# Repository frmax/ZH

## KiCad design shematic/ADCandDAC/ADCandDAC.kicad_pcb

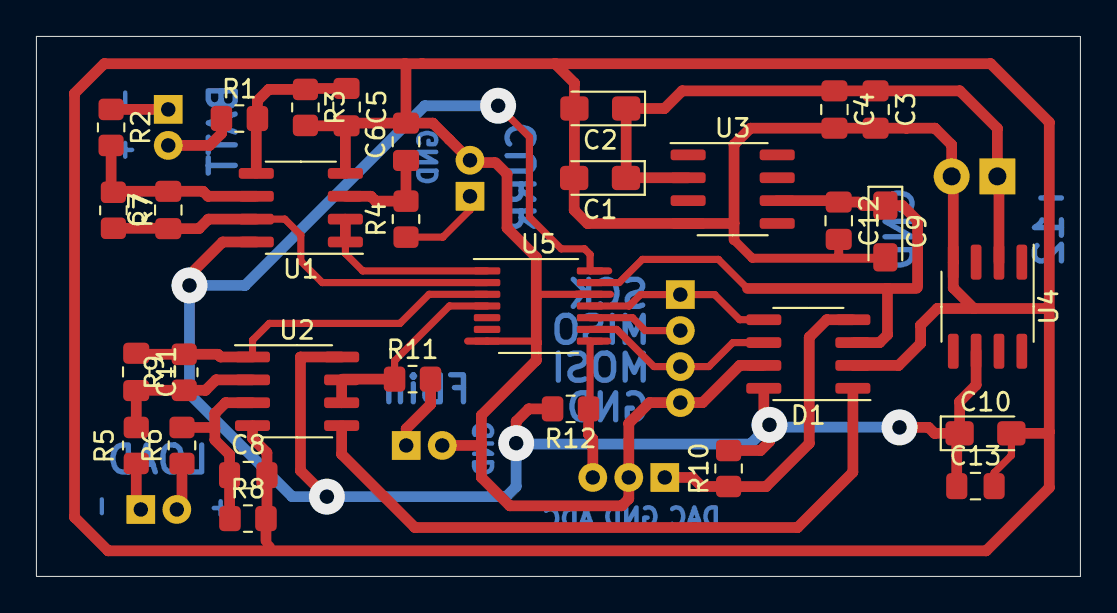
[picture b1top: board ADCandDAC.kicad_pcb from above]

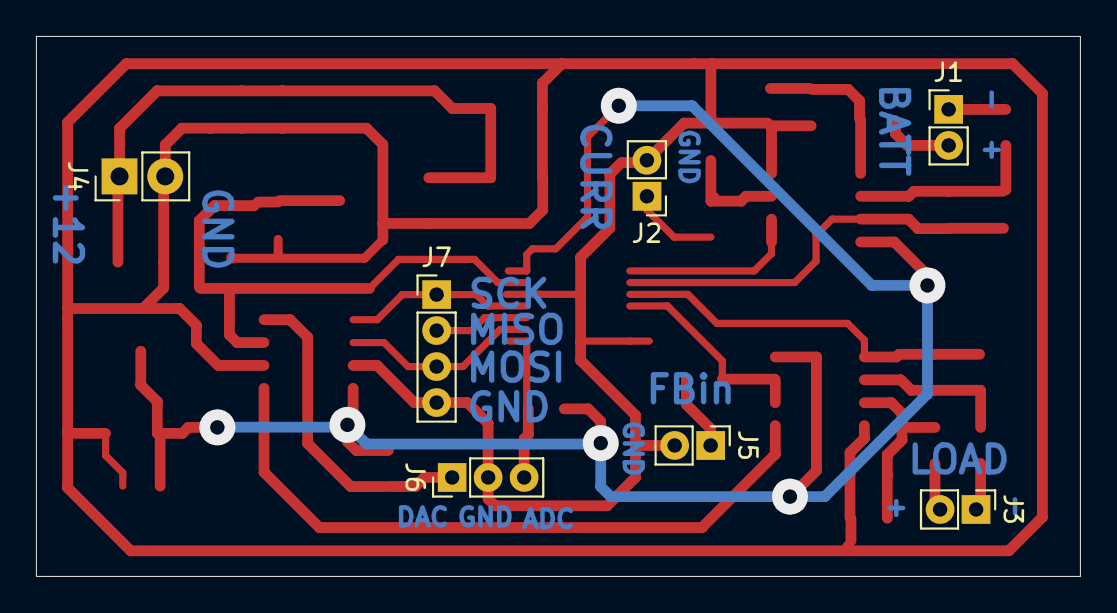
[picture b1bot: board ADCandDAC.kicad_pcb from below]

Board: 2 copper layers, 58.0 x 30.0 mm, 38 parts (7 on the bottom side), 25 nets.

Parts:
C1, C2: 10u; CP_EIA-3216-18_Kemet-A_Pad1.58x1.35mm_HandSolder
C3, C4, C5, C6, C7, C8, C11, C12, C13: 100n; C_0805_2012Metric_Pad1.18x1.45mm_HandSolder
C9, C10: 1u; CP_EIA-3216-18_Kemet-A_Pad1.58x1.35mm_HandSolder
D1: dac8830; SOIC-8_3.9x4.9mm_P1.27mm
J1: Battery; PinHeader_1x02_P2.00mm_Vertical
J2: Current; PinHeader_1x02_P2.00mm_Vertical
J3: Loading; PinHeader_1x02_P2.00mm_Vertical
J4: VCC_12V; PinHeader_1x02_P2.54mm_Vertical
J5: FBin; PinHeader_1x02_P2.00mm_Vertical
J6: CS; PinHeader_1x03_P2.00mm_Vertical
J7: SPI; PinHeader_1x04_P2.00mm_Vertical
R1, R2, R5, R6: 10k; R_0805_2012Metric_Pad1.20x1.40mm_HandSolder
R3, R4, R7, R8, R9: 1k; R_0805_2012Metric_Pad1.20x1.40mm_HandSolder
R10, R12: 100k; R_0805_2012Metric_Pad1.20x1.40mm_HandSolder
R11: 5,9k; R_0805_2012Metric_Pad1.20x1.40mm_HandSolder
U1, U2: AD8552ARZ; SOIC-8_3.9x4.9mm_P1.27mm
U3: REF198; SOIC-8_3.9x4.9mm_P1.27mm
U4: REF195; SOIC-8_3.9x4.9mm_P1.27mm
U5: MCP3204; TSSOP-14_4.4x5mm_P0.65mm

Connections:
/DACgen: D1.1, U2.5
/REF+4: C9.1, C12.1, D1.3, U3.6, U5.13
/REF+5: C10.1, C13.1, D1.8, R10.2, R12.2, U1.8, U2.8, U4.6, U5.14
ADC: J6.3, R12.1, U5.8
DAC: D1.4, J6.1, R10.1
GND: C1.2, C2.2, C3.2, C4.2, C5.2, C6.2, C8.2, C9.2, C10.2, C12.2, C13.2, D1.2, D1.7, J2.2, J4.2, J5.2, J6.2, J7.4, R3.2, R8.2, U1.4, U2.4, U3.4, U4.4, U5.7, U5.12
MISO: J7.2, U5.10
MOSI: D1.6, J7.3, U5.9
unnamed: C5.1, R1.2, R3.1, U1.5
unnamed: C6.1, R4.2, U1.3
unnamed: C7.1, R7.2, U1.7, U5.2
unnamed: C7.2, R2.2, R7.1, U1.6
unnamed: C8.1, R6.2, R8.1, U2.3
unnamed: C11.1, R9.2, U2.1, U5.3
unnamed: C11.2, R5.2, R9.1, U2.2
unnamed: J1.1, R2.1
unnamed: J1.2, R1.1
unnamed: J2.1, R4.1
unnamed: J3.1, R5.1
unnamed: J3.2, R6.1
unnamed: J5.1, R11.2
unnamed: R11.1, U2.6, U2.7, U5.4
unnamed: U1.1, U1.2, U5.1
SCK: D1.5, J7.1, U5.11
VCC_12V: C1.1, C2.1, C3.1, C4.1, J4.1, U3.2, U4.2

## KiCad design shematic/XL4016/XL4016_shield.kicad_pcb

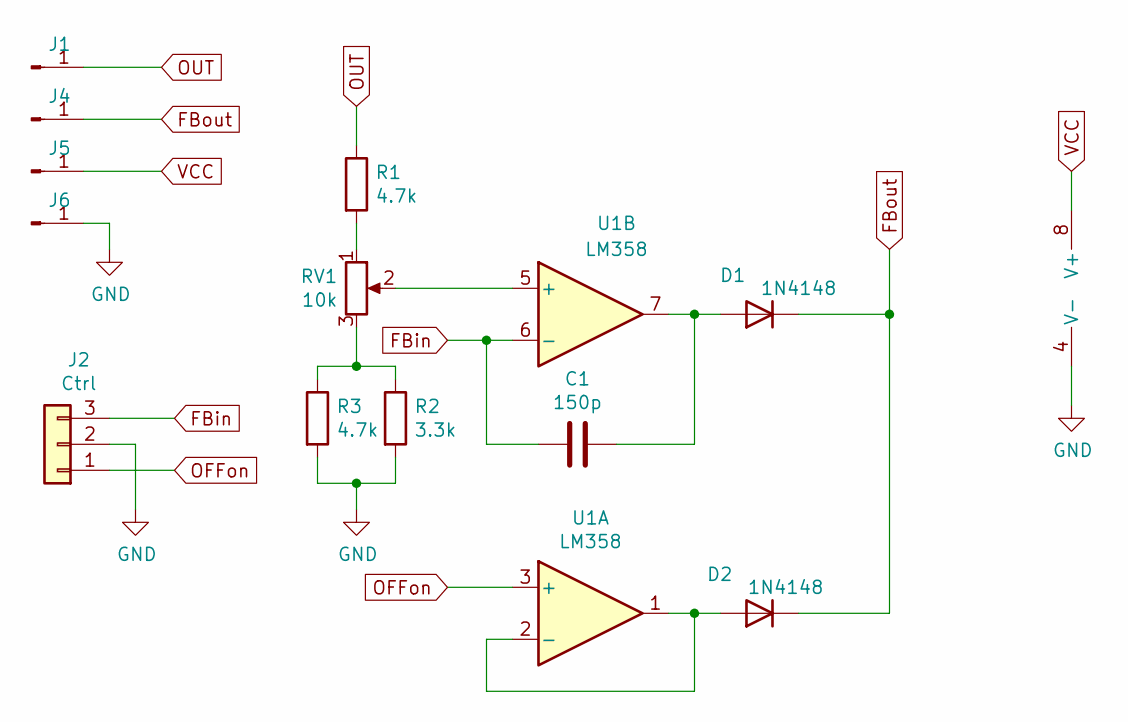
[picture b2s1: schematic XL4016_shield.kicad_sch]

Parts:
C1: 150p; C_0603_1608Metric_Pad1.08x0.95mm_HandSolder
D1, D2: 1N4148; D_SOD-123
J1: OUT+; Pin_D0.7mm_L6.5mm_W1.8mm_FlatFork
J2: Ctrl; PinHeader_1x03_P2.54mm_Vertical
J4: FBout; Pin_D0.7mm_L6.5mm_W1.8mm_FlatFork
J5: VCC; Pin_D0.7mm_L6.5mm_W1.8mm_FlatFork
J6: GND; Pin_D0.7mm_L6.5mm_W1.8mm_FlatFork
R1, R3: 4.7k; R_0603_1608Metric_Pad0.98x0.95mm_HandSolder
R2: 3.3k; R_0603_1608Metric_Pad0.98x0.95mm_HandSolder
RV1: 10k; Potentiometer_Bourns_3386C_Horizontal
U1: LM358; SO-8_3.9x4.9mm_P1.27mm

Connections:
FBin: C1.2, J2.3, U1.6 (-)
FBout: D1.1 (K), D2.1 (K), J4.1
GND: J2.2, J6.1, R2.2, R3.2, U1.4 (V-)
unnamed: C1.1, D1.2 (A), U1.7
unnamed: D2.2 (A), U1.1, U1.2 (-)
unnamed: R1.2, RV1.1
unnamed: R2.1, R3.1, RV1.3
unnamed: RV1.2, U1.5 (+)
OFFon: J2.1, U1.3 (+)
OUT: J1.1, R1.1
VCC: J5.1, U1.8 (V+)

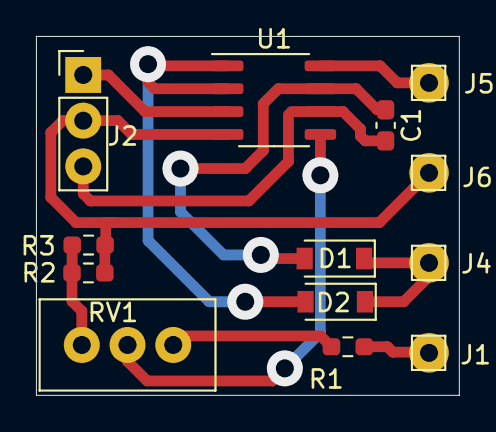
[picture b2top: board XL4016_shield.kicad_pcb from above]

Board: 2 copper layers, 23.5 x 19.9 mm, 13 parts (0 on the bottom side), 11 nets.

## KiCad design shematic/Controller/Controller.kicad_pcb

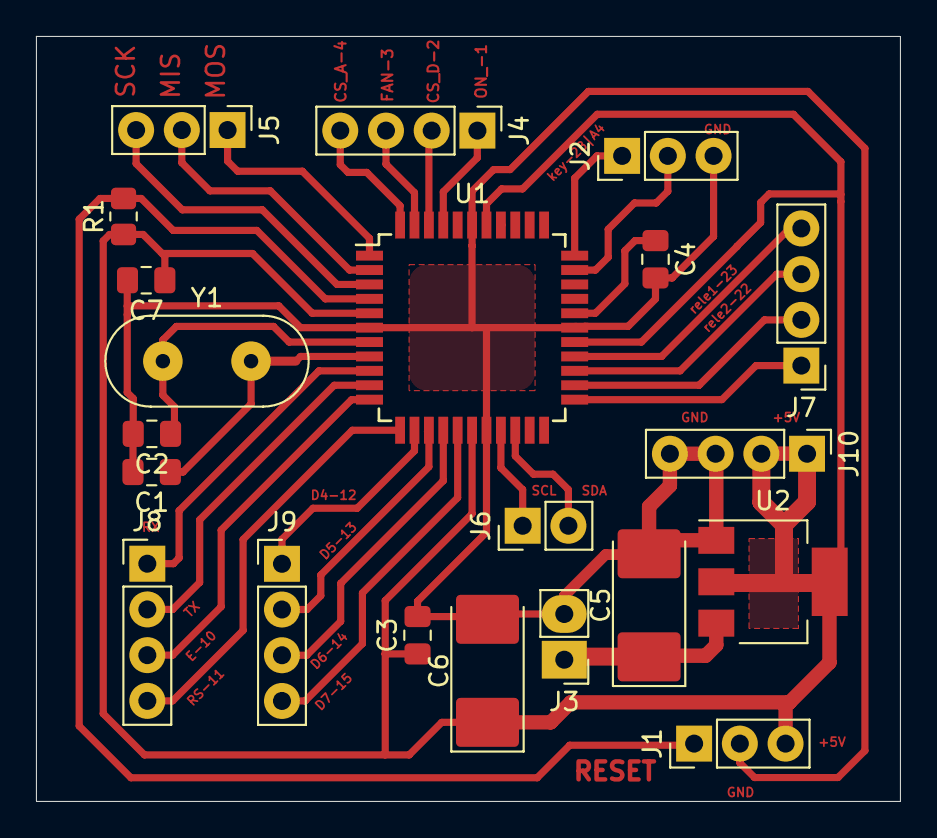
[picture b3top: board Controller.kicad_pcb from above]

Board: 2 copper layers, 48.0 x 42.5 mm, 21 parts (0 on the bottom side), 30 nets.

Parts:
C1, C2: 20p; C_0805_2012Metric_Pad1.18x1.45mm_HandSolder
C3, C4, C7: 100n; C_0805_2012Metric_Pad1.18x1.45mm_HandSolder
C5, C6: 47u; CP_EIA-7132-20_AVX-U_Pad2.72x3.50mm_HandSolder
J1: RESET; PinHeader_1x03_P2.54mm_Vertical
J2: Analog; PinHeader_1x03_P2.54mm_Vertical
J3: +12; PinHeader_1x02_P2.54mm_Vertical
J4: CS_FAN_ONOFF; PinHeader_1x04_P2.54mm_Vertical
J5: SPI; PinHeader_1x03_P2.54mm_Vertical
J6: I2C; PinHeader_1x02_P2.54mm_Vertical
J7: RELE_T; PinHeader_1x04_P2.54mm_Vertical
J8: RxTx/Display_1; PinHeader_1x04_P2.54mm_Vertical
J9: Display_2; PinHeader_1x04_P2.54mm_Vertical
J10: +5_GND; PinHeader_1x04_P2.54mm_Vertical
R1: 10k; R_0805_2012Metric_Pad1.20x1.40mm_HandSolder
U1: ATmega16A-AU; TQFP-44_10x10mm_P0.8mm
U2: AMS1117-5.0; SOT-223-3_TabPin2
Y1: Crystal; Crystal_HC18-U_Vertical

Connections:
+5V: C3.1, C6.1, C7.1, J1.3, J10.1, J10.2, R1.1, U1.5, U1.17, U1.27, U1.38, U2.2
+12V: C5.1, J3.1, U2.3
/CS_A-4: J4.4, U1.44
/CS_D-2: J4.2, U1.42
/D4-12: J9.1, U1.13
/D5-13: J9.2, U1.14
/D6-14: J9.3, U1.15
/D7-15: J9.4, U1.16
/E-10: J8.3, U1.11
/FAN-3: J4.3, U1.43
/KEY_-28|A4: J2.1, U1.33
/MISO: J5.2, U1.2
/MOSI: J5.1, U1.1
/ON_-1: J4.1, U1.41
/RELE_1-23: J7.4, U1.26
/RELE_2-22: J7.3, U1.25
/RS-11: J8.4, U1.12
/RX: J8.1, U1.9
/SCK: J5.3, U1.3
/SCL: J6.1, U1.19
/SDA: J6.2, U1.20
/TX: J8.2, U1.10
GND: C1.2, C2.2, C3.2, C4.2, C5.2, C6.2, C7.2, J1.2, J2.3, J3.2, J10.3, J10.4, U1.6, U1.18, U1.28, U1.39, U2.1
unnamed: C1.1, U1.8, Y1.2
unnamed: C2.1, U1.7, Y1.1
unnamed: C4.1, U1.29
unnamed: J2.2, U1.32
unnamed: J7.1, U1.23
unnamed: J7.2, U1.24
RESET: J1.1, R1.2, U1.4

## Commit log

2022-09-27 First. Add all files
